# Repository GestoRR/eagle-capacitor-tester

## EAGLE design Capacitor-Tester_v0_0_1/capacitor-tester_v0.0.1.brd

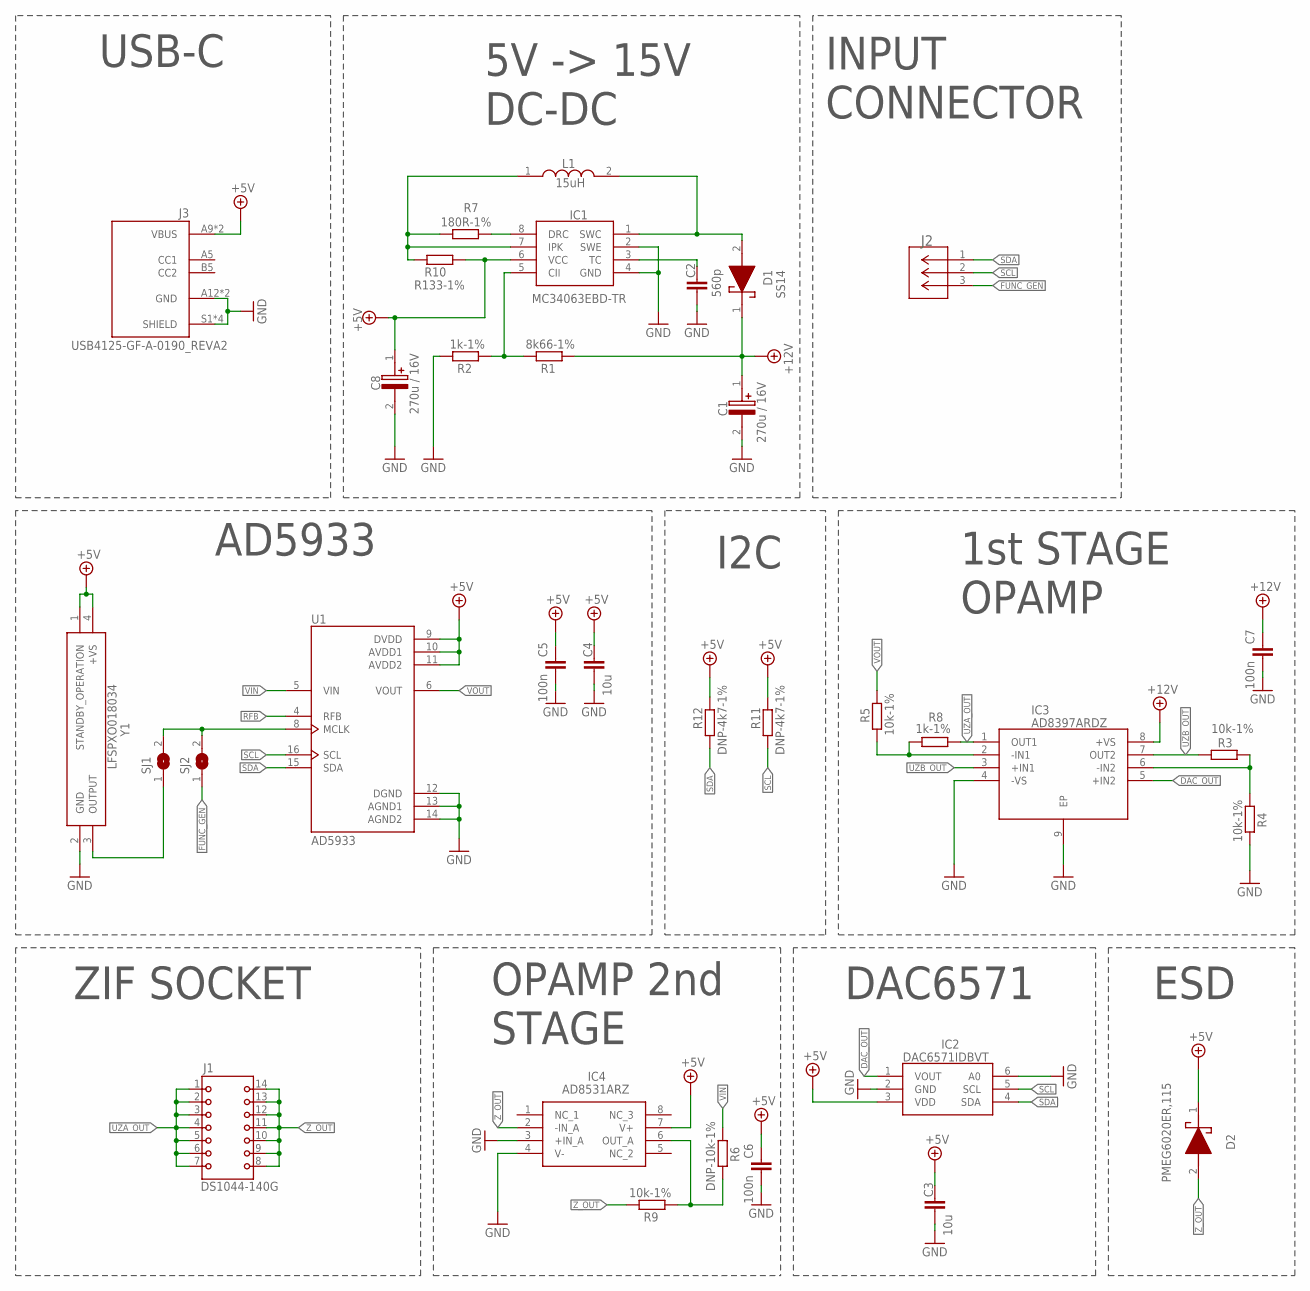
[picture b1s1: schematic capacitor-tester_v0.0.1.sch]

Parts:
C1, C8: 270u / 16V; EEE0JA331XP
C2: 560p; C0603
C3, C4: 10u; C0603
C5, C6, C7: 100n; C0603
D1: SS14; DIOM5227X270N
D2: PMEG6020ER,115; PMEG6020ER115
IC1: MC34063EBD-TR; SOIC127P600X175-8N
IC2: DAC6571IDBVT; SOT95P280X145-6N
IC3: AD8397ARDZ; SOIC127P600X175-9N
IC4: AD8531ARZ; SOIC127P600X175-8N
J1: DS1044-140G; CONNFLY_DS1044-140G
J2: 250-103; CONN3_250-103_WAG
J3: USB4125-GF-A-0190_REVA2; GCT_USB4125-GF-A-0190_REVA2
L1: 15uH; SDR0604330KL
R1: 8k66-1%; R0603
R2, R8: 1k-1%; R0603
R3, R4, R5, R9: 10k-1%; R0603
R6: DNP-10k-1%; R0603
R7: 180R-1%; R0603
R10: R133-1%; R0603
R11, R12: DNP-4k7-1%; R0603
SJ1, SJ2: SJW
U1: AD5933; SOP65P780X200-16N
Y1: LFSPXO018034

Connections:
+5V: C3.1, C4.1, C5.1, C6.1, C8.1 (+), D2.1 (K), IC1.6 (VCC), IC2.3 (VDD), IC4.7 (V+), J3.A9 (VBUS), J3.B9 (VBUS), R10.1, R11.2, R12.2, U1.9 (DVDD), U1.10 (AVDD1), U1.11 (AVDD2), Y1.1 (STANDBY_OPERATION), Y1.4 (+VS)
+12V: C1.1 (+), C7.1, D1.1 (K), IC3.8 (+VS), R1.1
DAC_OUT: IC2.1 (VOUT), IC3.5 (+IN2)
FUNC_GEN: J2.3, SJ2.1
GND: C1.2 (-), C2.2, C3.2, C4.2, C5.2, C6.2, C7.2, C8.2 (-), IC1.2 (SWE), IC1.4 (GND), IC2.2 (GND), IC2.6 (A0), IC3.4 (-VS), IC3.9 (EP), IC4.3 (+IN_A), IC4.4 (V-), J3.A12 (GND), J3.B12 (GND), J3.S1 (SHIELD), J3.S2 (SHIELD), J3.S3 (SHIELD), J3.S4 (SHIELD), R2.2, R4.2, U1.12 (DGND), U1.13 (AGND1), U1.14 (AGND2), Y1.2 (GND)
MCLK: SJ1.1, Y1.3 (OUTPUT)
unnamed: IC4.6 (OUT_A), R6.2, R9.1
unnamed: IC3.2 (-IN1), R5.1, R8.1
unnamed: D1.2 (A), IC1.1 (SWC), L1.2
unnamed: SJ1.2, SJ2.2, U1.8 (MCLK)
unnamed: IC1.5 (CII), R1.2, R2.1
unnamed: IC1.8 (DRC), R7.1
unnamed: C2.1, IC1.3 (TC)
unnamed: IC1.7 (IPK), L1.1, R7.2, R10.2
unnamed: IC3.6 (-IN2), R3.2, R4.1
RFB: U1.4 (RFB)
SCL: IC2.5 (SCL), J2.2, R11.1, U1.16 (SCL)
SDA: IC2.4 (SDA), J2.1, R12.1, U1.15 (SDA)
UZA_OUT: IC3.1 (OUT1), J1.1, J1.2, J1.3, J1.4, J1.5, J1.6, J1.7, R8.2
UZB_OUT: IC3.3 (+IN1), IC3.7 (OUT2), R3.1
VIN: R6.1, U1.5 (VIN)
VOUT: R5.2, U1.6 (VOUT)
Z_OUT: D2.2 (A), IC4.2 (-IN_A), J1.8, J1.9, J1.10, J1.11, J1.12, J1.13, J1.14, R9.2

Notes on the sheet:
AD5933
USB-C
INPUT CONNECTOR
I2C
1st STAGE OPAMP
ZIF SOCKET
5V -> 15V DC-DC
DAC6571
OPAMP 2nd STAGE
ESD

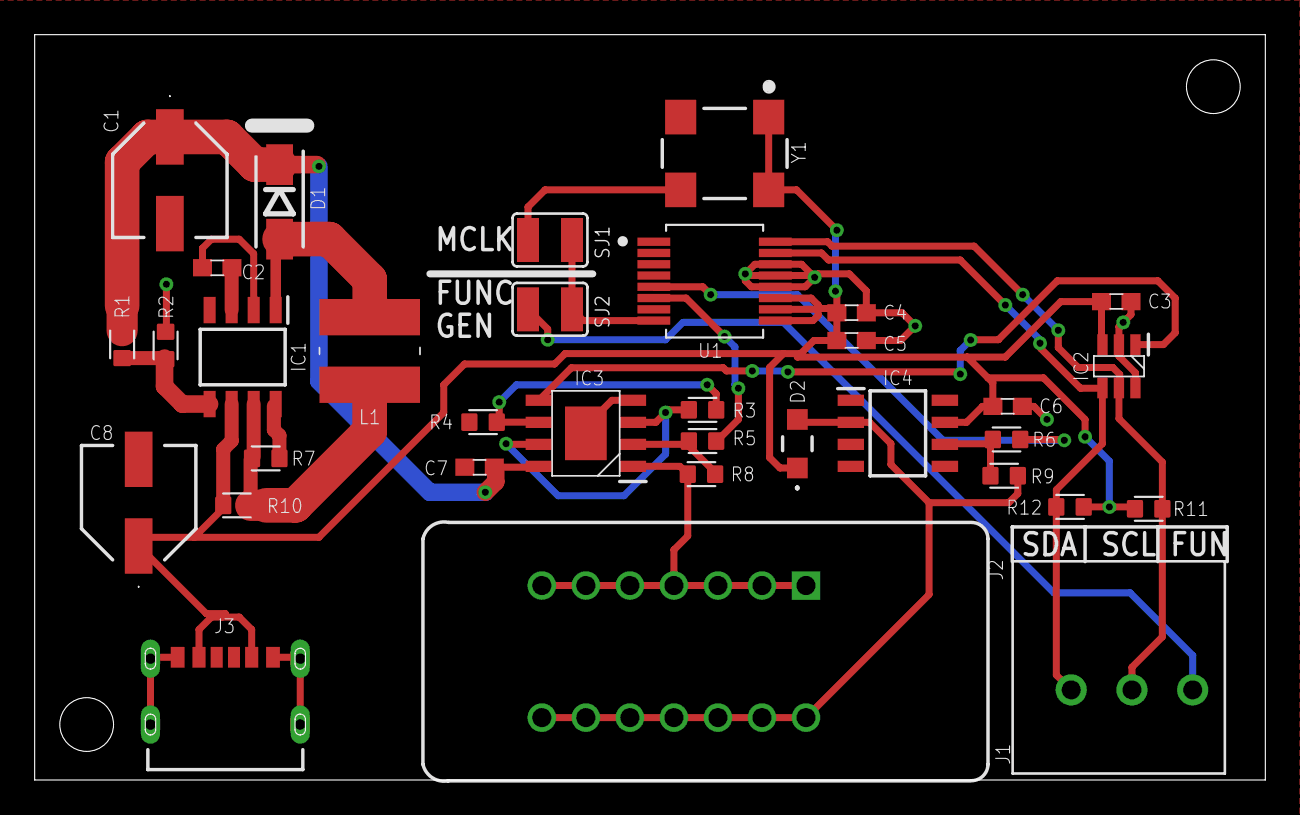
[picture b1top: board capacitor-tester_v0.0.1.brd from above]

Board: 2 copper layers, 71.0 x 43.0 mm, 34 parts (0 on the bottom side), 22 nets.

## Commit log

2025-05-21 Init
2025-05-22 v0.0.1 - Finished the first stage of AD5933 opamp and added usb c connector for the power supply
2025-05-22 v0.0.1 - Added two stages of the opamps. Need to add boost converter for the second opamp
2025-05-25 v0.0.1 - Added 5V -> 15V boost converter for the second stage opamp.
2025-05-25 v0.0.1 - Added input connector
2025-05-25 v0.0.1 - Fix in the schematic. Bad label. Version before changing the input connector to Wago 250-103
2025-05-25 v0.0.1 - Changed wago 250-102 for 250-103 and connected FUNC_GEN to the input connector
2025-06-12 v0.0.1 - Version control. Added DAC6571
2025-06-12 v0.0.1 - Version control before big changes in the schematic
2025-06-12 v0.0.1 - Changed both stages of the opamps. Need to change from 15V to 12V
2025-06-13 v0.0.1 - Changed boost converter to +12V on output and added shottky diode
2025-10-09 v0.0.1 - Changed L1
2025-10-09 IN PROGRESS - arranging elements
2025-10-09 v0.0.1 - Routed traces
2025-10-09 v0.0.1 - CMD renumber + tnames + bnames
2025-10-14 v0.0.1 - Revert to commit b06d3d6
2025-10-14 v0.0.1 - Added text to the Solder Jumpers
2025-10-26 v0.0.1 - Trying different component layout. Finished brd
2025-11-04 v0.0.1 - Different component layout and trace placement
2025-11-12 IN PROGRESS - v0.0.1 new component layout
2025-11-12 IN PROGRESS - v0.0.1 routing traces
2025-11-12 IN PROGRESS - Trace routing
2025-11-12 IN PROGRESS - Finished routing traces
2025-11-12 V0.0.1 - Finished .brd
2025-11-18 v0.0.1 - Changes in .brd

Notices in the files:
parts and their libraries:
COPYRIGHT: Copyright (C) 2025 Ultra Librarian. All rights reserved.
